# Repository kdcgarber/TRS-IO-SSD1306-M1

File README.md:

# TRS-IO with a SSD1306 LCD display for my Model 1
<br>

These are my notes for the build of this version of my TRS-IO<br>
This repo is, like my other repo, based on a snapshot of https://github.com/apuder/TRS-IO commit f2acde6.<br>
That original repo is an amazing piece of hardware/software that provides new feature to my retro TRS-80 model 1<br>
Thanks for making that project hardware design and code avialable for others like me to use on our retro machines.

I’ve built several TRS-IO boards (the earlier versions are on my other GitHub repo), and I’ve now rebuilt them using this updated design.<br>

One challenge I ran into was keeping track of the IP address for each my TRS-IO's.<br>
So, when multiple TRS-IO units are powered on at the same time, it becomes difficult to know which device you’re actually connected to.<br>

To solve that —and mostly just for fun and to learn more— I extended the original design to include a small status display.<br>
This makes it easy to see the assigned IP address and other useful information directly from the TRS-IO itself.<br>

Because this codebase has diverged from the original TRS-IO backported source, I can no longer pull an upstream updates if there are any.<br>
If the original repository is updated in the future, those changes won’t be reflected here unless manually merged.<br>
That said, most current development in this space appears to be shifting toward TRS-IO++, so upstream changes may be minimal going forward.<br>

These notes document the steps I took to configure this new hardware design with my modified software.<br>
They are just notes. They’re primarily for my own reference, but they may also be helpful to others following a similar path.<br>

The new, smaller PCB files that include the display are available in this repo.<br>

The only real difference for the hardware of my board is the part layout <br>
and removing the LED and its resistors to be replaced with a SSD1306 display. <br>
Any TRS-IO could be changed to replace the LED, it just has no mount to hold the display in place, though one can be created. <br>

<table>
  <tr>
	<td></td>
	<td></td>
  </tr>
</table>

<bre>

## 📂 Content in repository

	.
	├── DebugNotes.txt                       - Notes to setup my PC to view output from the ESP-WROOM-32 usb port
	├── SDcardM1auto.zip                     - SD card files for the SMB share
	├── 3d                                   - STL files to 3D print a case for the new TRS-IO-SSD1306
	├── buildFiles                           - FPGA file
	├── doc                                  - Doc from the original site
	├── examples                             - Code samples form the Orignal Site
	├── images                               - Images for the github pages
	├── kicad-SSD1306                        - Contains the kicad data for the project PCB
	├── src                                  - This is the altered code for the ESP-WROOM-32
	└── src/esp/ESP-WROOOM-32-Deployment     - Compiled Binary ESP files ready for deployment

<br>

## The hardware build and BOM

All of the files for the PCB are in the kicad-SSD1306 directory.<br>
I sent the files to PCBWay to have them created.<br>
Since you pay per square millimeter of board, by placing all the surface mount components on the back sidek, I saved money on the board cost.<br>
In my final builds I opted to mount the FPGA, ESP32, and display directly to the board to decrease the thickness of the board.<br>
I've done both ways, but in the end, since these are dedicated to this, I went with directly soldering them with no sockets.<br>

<table>
  <tr>
    <td></td>
    <td></td>
    <td></td>
  </tr>
  <tr>
    <td></td>
    <td></td>
  </tr>
</table>

<br>
The BOM shows the parts needed and their layout and placement.<br>

<a href="https://kdcgarber.github.io/githubPages-htmlfiles/TRS-IO-SSD1306%20bom/ibom.html" target="_blank">Parts list.</a>
<br>

## There are two paths to get the code deployed to your ESP-WROOM-32.

1 Build the files from source and deploy.<br>
2 Just use the pre-built files to flash your ESP.<br>

<br>
<br>

## Option 1 - The Software build for the ESP-WROOM-32

These notes for the code build are based on the original notes of my TRS-IO build.<br>
The code in this repo already has my code changes in it, so no to alter any code by hand.<br>
I built this for my enjoyment and to learn and have fun.<br>
These changes may not be the best code they could be, but if anyone wants to use it, they can.<br>

I used the ESP-WROOM-32 esp controller (no PSRAM) - https://www.amazon.com/dp/B0B764963C<br>
And I used the Tang Nano 9K FPGA - https://www.aliexpress.us/item/3256804089255675.html<br>

I did this code build on Ubuntu 24.04, as a non-root account<br>

### Prep - installing required components<br>
&nbsp;&nbsp;&nbsp;&nbsp;sudo apt upgrade<br>
### Packages for Espressif<br>
&nbsp;&nbsp;&nbsp;&nbsp;sudo apt-get install git wget flex bison gperf python3 python3-pip python3-setuptools cmake ninja-build ccache libffi-dev libssl-dev dfu-util libusb-1.0-0 python3-virtualenv<br>
###  Packages for TRS-IO<br>
&nbsp;&nbsp;&nbsp;&nbsp;sudo apt-get install z80asm sdcc sdcc-libraries<br>
###  Some fixes for linking libraries that are needed by TRS-IO<br>
&nbsp;&nbsp;&nbsp;&nbsp;sudo mkdir -p /lib/z80/<br>
&nbsp;&nbsp;&nbsp;&nbsp;sudo ln -s /usr/share/sdcc/lib/z80/z80.lib /lib/z80/z80.lib<br>
###  Python3 as default:<br>
&nbsp;&nbsp;&nbsp;&nbsp;sudo apt-get install python3 python3-pip python3-setuptools<br>
&nbsp;&nbsp;&nbsp;&nbsp;sudo ln -s /usr/bin/python3 /usr/bin/python<br>
<br>

###  Install ESP-IDF<br>
cd ~/<br>
mkdir esp<br>
cd esp<br>
git clone -b v4.4.7 --recurse-submodules https://github.com/espressif/esp-idf.git<br>
cd ~/esp/esp-idf<br>
./install.sh esp32<br>

### clone this repo
cd ~/esp<br>
git clone --recurse-submodules https://github.com/kdcgarber/TRS-IO-SSD1306-M1.git<br>

### TRS-IO stuff<br>
.  ~/esp/esp-idf/export.sh<br>

## Compile and Flash the ESP<br>
cd ~/esp/TRS-IO-SSD1306-M1/src/esp<br>
idf.py fullclean<br>
make BOARD=trs-io-m1-v14 build<br>

The build will show many warnings, but if it completes with no errors, the rest should be good.<br>
At the bottom of its output, it lists the command to run. The port needs to be changed to match the correct port.<br>

Sometimes while doing the flash, it fails. If it does, just try it again and it will load.<br><br>
~/esp/esp-idf/components/esptool_py/esptool/esptool.py -p /dev/ttyUSB0  -b 460800 --before default_reset --after hard_reset --chip esp32  write_flash --flash_mode dio --flash_size detect --flash_freq 40m 0x1000 build/bootloader/bootloader.bin 0x8000 build/partition_table/partition-table.bin 0x10000 build/trs-io.bin 0x190000 build/html.bin<br>

<br><br><br>

## 💾 Option 2 - Just use the pre-built bin files
<br>
This path is to flash the ESP-WROOM-32 from the provided files without a full code rebuild. <br>
The code does not need to be recompiled unless you are making changes or just want to.
This directory contains 4 files that are the files needed for the ESP: src/esp/ESP-WROOOM-32-Deployment<br>
<br>
• bootloader.bin<br>
• html.bin<br>
• partition-table.bin<br>
• trs-io.bin<br>
<br>

To use these files you'll need to to install ESPTOOL and then deploy the code.<br>
I did my file flash from the files via a windows 11 PC.<br>

From a windows command shell (CMD)<br>
### Check that Python and PIP are installed and install if they are not found. 
python --version<br>
&nbsp;&nbsp;Python 3.12.10<br>

pip --version <br>
&nbsp;&nbsp;pip 25.3 from C:\Users\toddr\AppData\Local\Packages\PythonSoftwareFoundation.Python.3.12_qbz5n2kfra8p0\LocalCache\local-packages\Python312\site-packages\pip (python 3.12)<br>

### This installs the ESPTOOL
pip install esptool<br>

### Add a shortcut to get to the path to use the ESPTOOL
doskey esptool="C:\Users\toddr\AppData\Local\Packages\PythonSoftwareFoundation.Python.3.12_qbz5n2kfra8p0\LocalCache\local-packages\Python312\Scripts\esptool.exe" $* <br>

ESPTOOL should now work<br>

Just enter "esptool", it should give the default help windows message<br>
Plug your ESP-WROOM-32 in via the usb port to your windows 11 pc.<br>

### Now to find the COM port
With the esp plugged into the laptop in windows 11, "mode" will show the COM it's connected to.<br>
The COM will need to be used on the flash command<br>

mode<br>

Status for device COM5:<br>
Baud:            115200<br>
Parity:          None<br>
Data Bits:       8<br>
Stop Bits:       1<br>
Timeout:         OFF<br>
XON/XOFF:        OFF<br>
CTS handshaking: OFF<br>
DSR handshaking: OFF<br>
DSR sensitivity: OFF<br>
DTR circuit:     OFF<br>
RTS circuit:     OFF<br>
<br>

### Move to your code repo and move to the src/esp/ directory. <br>
cd "C:\Users\toddr\OneDrive\Shared\Todd\GitHub\trsnic-ssd1306\src\esp"<br>

There will be 4 bin files in the directory ESP-WROOOM-32-Deployment which will be flashed to the ESP. <br>
 ### Run this command
(Replace COM5 with your actual COM port number if necessary.) <br>

esptool --chip esp32 --port COM5 --baud 460800 write-flash --flash-mode dio --flash-size detect --flash-freq 40m -z 0x1000 ESP-WROOOM-32-Deployment\bootloader.bin 0x8000 ESP-WROOOM-32-Deployment\partition-table.bin 0x10000 ESP-WROOOM-32-Deployment\trs-io.bin 0x190000 ESP-WROOOM-32-Deployment\html.bin <br>

This should flash the ESP and it will now be ready to use.<br>

# Flash the FPGA

### Install openFPGALoader

apt install \\<br>
  git \\<br>
  gzip \\<br>
  libftdi1-2 \\<br>
  libftdi1-dev \\<br>
  libhidapi-hidraw0 \\<br>
  libhidapi-dev \\<br>
  libudev-dev \\<br>
  zlib1g-dev \\<br>
  cmake \\<br>
  pkg-config \\<br>
  make \\<br>
  g++

git clone https://github.com/trabucayre/openFPGALoader<br>
cd openFPGALoader<br>
mkdir build<br>
cd build<br>
cmake .. <br>
cmake --build .<br>
make install<br>

### The FPGA file is TRS-IO.fs<br>

cd  ~/esp/buildFiles<br>
openFPGALoader -b tangnano9k -f TRS-IO.fs

	EXAMPLE:
	root@thebox:/home/kdcgarber/esp/buildFiles# openFPGALoader -b tangnano9k -f TRS-IO.fs

	empty
	write to flash
	Jtag frequency : requested 6.00MHz   -> real 6.00MHz
	Parse file Parse TRS-IO.fs:
	Done
	DONE
	Jtag frequency : requested 2.50MHz   -> real 2.00MHz
	Erase SRAM DONE
	Erase FLASH DONE
	Erasing FLASH: [==================================================] 100.00%
	Done
	write Flash: [==================================================] 100.00%
	Done
	CRC check: Success

<br>

* There is also a newer version of the TRS-IO.fs that I now use. It provides higher resolution glyphs that can be used instead of the original TRS-IO.fs file. It is called TRS-IO-v1_4-HiRes.fs and can be flashed to replace the TRS-IO.fs I used originally.  
openFPGALoader -b tangnano9k -f TRS-IO-v1_4-HiRes.fs

## All done with the Install

After the install is complete, follow the notes on the TRS-IO site to bring up the trs-io.local access point<br> 
and start the configuration.<br>
The site also has the ROM boot loader for the FreHD to go on the SD card<br>
or the SMB (windows share or for me SAMBA share on my Linux server).<br>

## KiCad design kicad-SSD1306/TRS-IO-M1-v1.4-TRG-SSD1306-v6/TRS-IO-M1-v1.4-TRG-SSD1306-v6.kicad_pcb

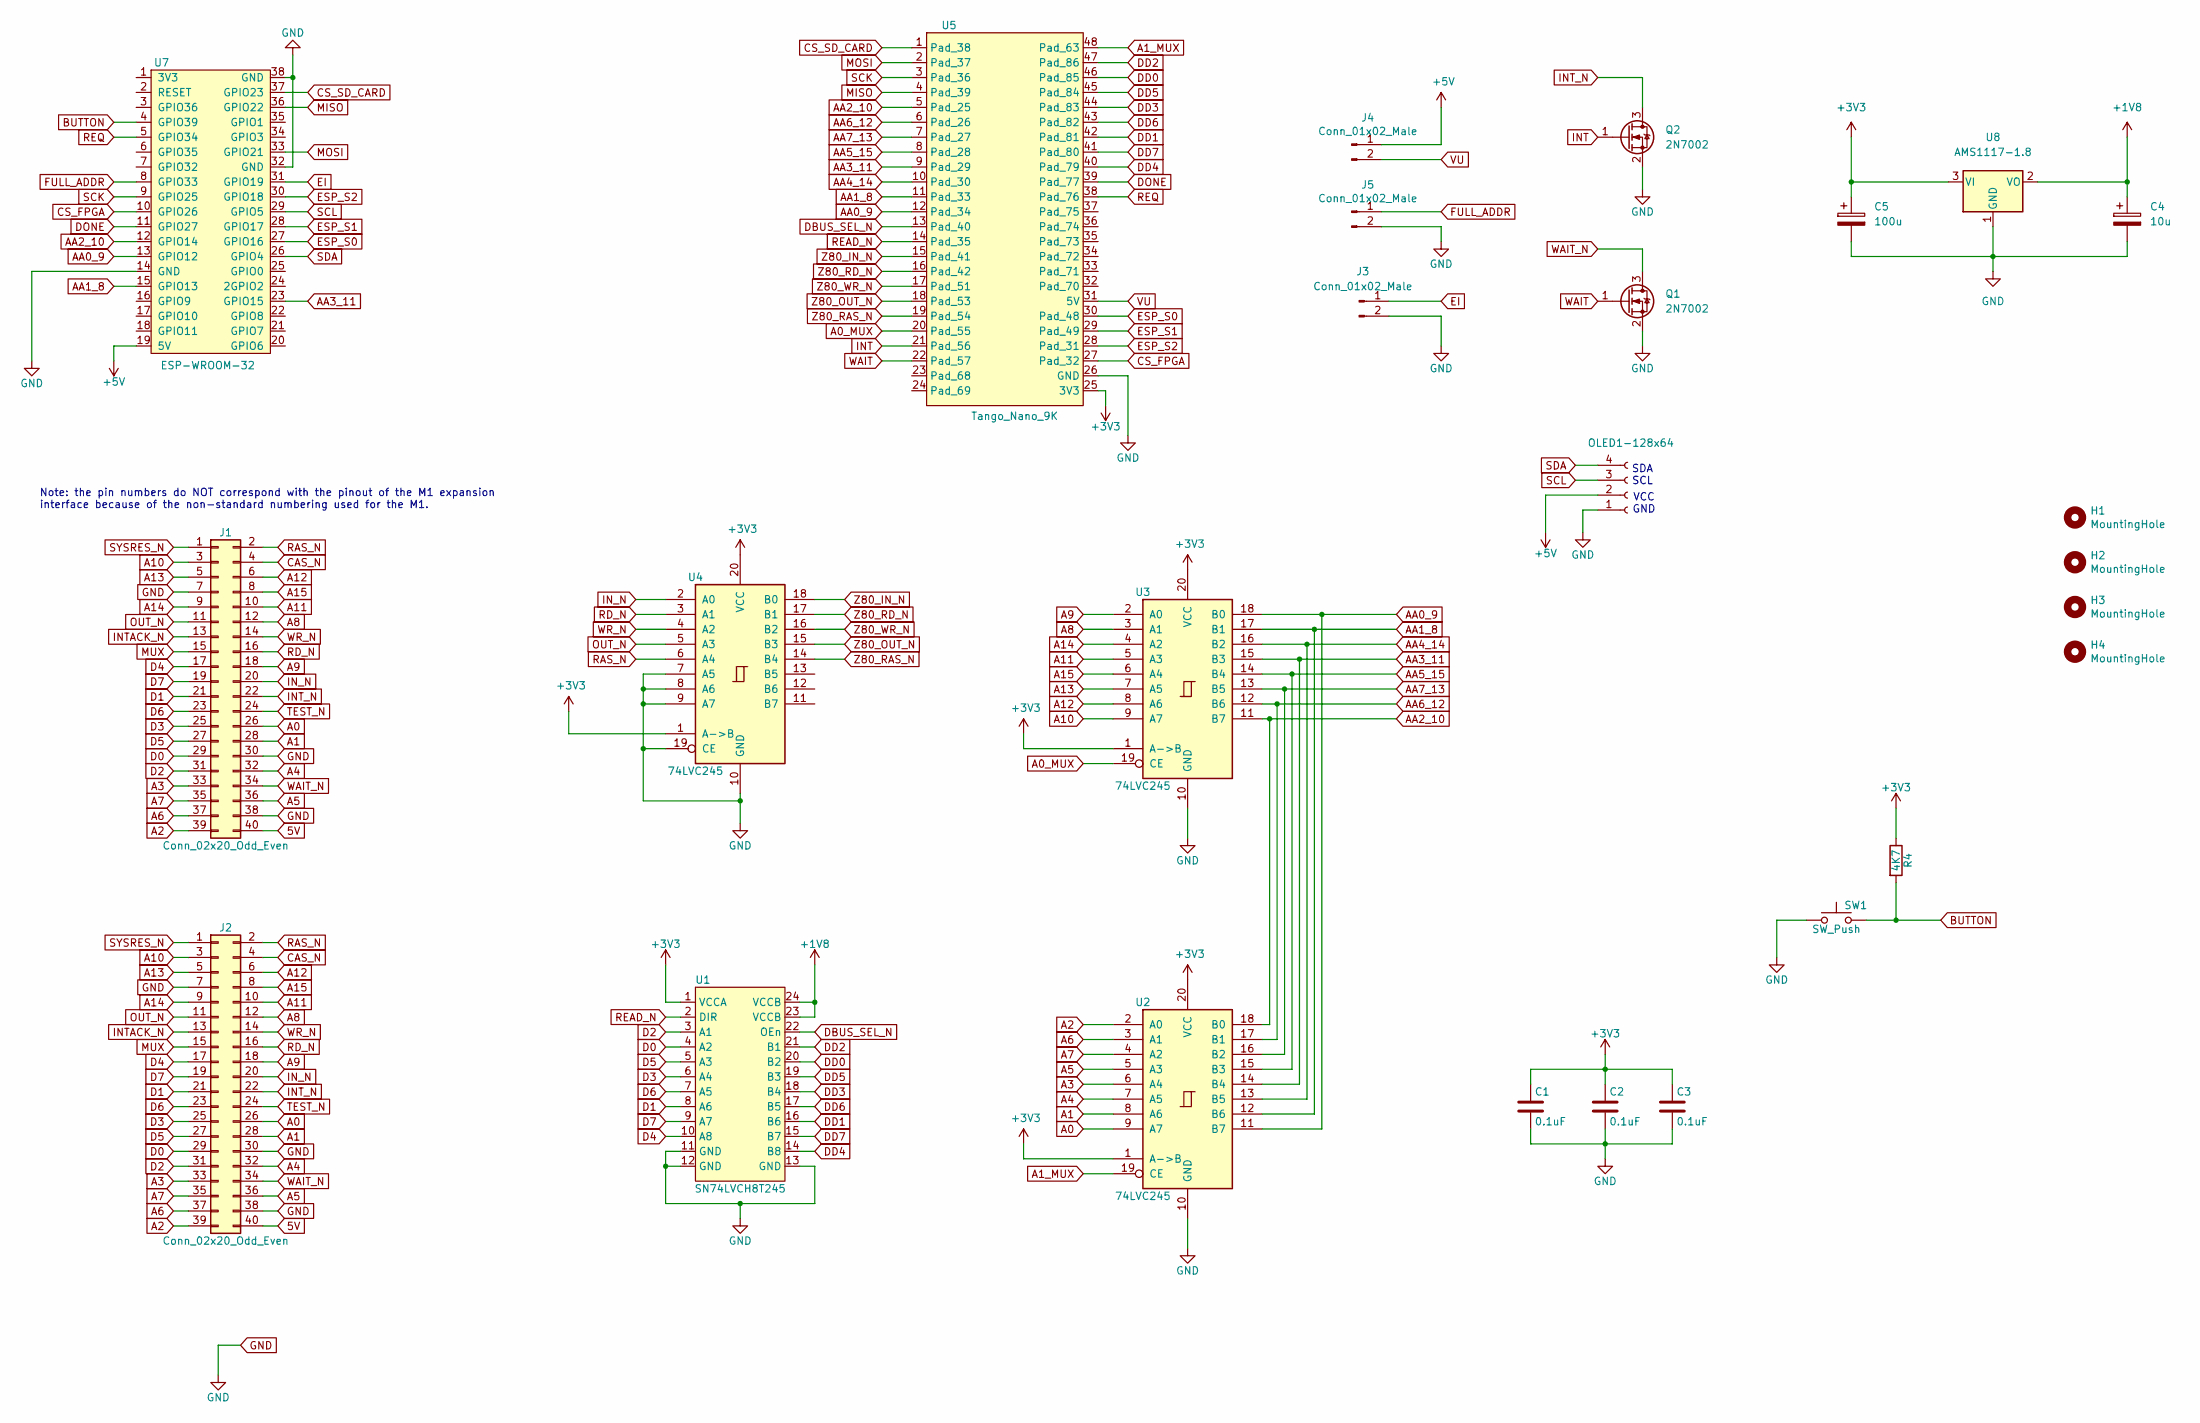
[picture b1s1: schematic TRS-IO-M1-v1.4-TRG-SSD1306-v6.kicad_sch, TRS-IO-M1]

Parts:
C1, C2, C3: 0.1uF; C_0805_2012Metric_Pad1.18x1.45mm_HandSolder
C4: 10u; C_1206_3216Metric_Pad1.33x1.80mm_HandSolder
C5: 100u; C_1206_3216Metric_Pad1.33x1.80mm_HandSolder
H1, H2, H3, H4: MountingHole; MountingHole_3mm_Pad_Via
J1: Conn_02x20_Odd_Even; PinHeader_2x20_P2.54mm_Vertical
J2: Conn_02x20_Odd_Even; TRSEDGE
J3, J4, J5: Conn_01x02_Male; PinHeader_1x02_P2.54mm_Vertical
OLED1-128x64: Conn_01x04_Socket; PinSocket_1x04_P2.54mm_Vertical
Q1, Q2: 2N7002; SOT-23
R4: 4K7; R_0805_2012Metric_Pad1.20x1.40mm_HandSolder
SW1: SW_Push; SW_PUSH_6mm_H9.5mm
U1: SN74LVCH8T245; TSSOP-24_4.4x7.8mm_P0.65mm
U2, U3, U4: 74LVC245; SSOP-20_5.3x7.2mm_P0.65mm_slim
U5: Tango_Nano_9K; DIP-48_W22.9mm
U7: ESP-WROOM-32; DIP-38_W22.9mm
U8: AMS1117-1.8; SOT-223-3_TabPin2

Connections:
5V: J1.40, J2.40
+1V8: C4.1, U1.23 (VCCB), U1.24 (VCCB), U8.2 (VO)
+3V3: C1.1, C2.1, C3.1, C5.1, R4.1, U1.1 (VCCA), U2.1 (A->B), U2.20 (VCC), U3.1 (A->B), U3.20 (VCC), U4.1 (A->B), U4.20 (VCC), U5.25 (3V3), U8.3 (VI)
+5V: J4.1, OLED1-128x64.2, U7.19 (5V); also elsewhere on the board
A0: J1.26, J2.26, U2.9 (A7)
A0_MUX: U3.19 (CE), U5.20 (Pad_55)
A1: J1.28, J2.28, U2.8 (A6)
A1_MUX: U2.19 (CE), U5.48 (Pad_63)
A2: J1.39, J2.39, U2.2 (A0)
A3: J1.33, J2.33, U2.6 (A4)
A4: J1.32, J2.32, U2.7 (A5)
A5: J1.36, J2.36, U2.5 (A3)
A6: J1.37, J2.37, U2.3 (A1)
A7: J1.35, J2.35, U2.4 (A2)
A8: J1.12, J2.12, U3.3 (A1)
A9: J1.18, J2.18, U3.2 (A0)
A10: J1.3, J2.3, U3.9 (A7)
A11: J1.10, J2.10, U3.5 (A3)
A12: J1.6, J2.6, U3.8 (A6)
A13: J1.5, J2.5, U3.7 (A5)
A14: J1.9, J2.9, U3.4 (A2)
A15: J1.8, J2.8, U3.6 (A4)
AA0_9: U2.11 (B7), U3.18 (B0), U5.12 (Pad_34), U7.13 (GPIO12)
AA1_8: U2.12 (B6), U3.17 (B1), U5.11 (Pad_33), U7.15 (GPIO13)
AA2_10: U2.18 (B0), U3.11 (B7), U5.5 (Pad_25), U7.12 (GPIO14)
AA3_11: U2.14 (B4), U3.15 (B3), U5.9 (Pad_29), U7.23 (GPIO15)
AA4_14: U2.13 (B5), U3.16 (B2), U5.10 (Pad_30)
AA5_15: U2.15 (B3), U3.14 (B4), U5.8 (Pad_28)
AA6_12: U2.17 (B1), U3.12 (B6), U5.6 (Pad_26)
AA7_13: U2.16 (B2), U3.13 (B5), U5.7 (Pad_27)
BUTTON: R4.2, SW1.2, U7.4 (GPIO39)
CAS_N: J1.4, J2.4
CS_FPGA: U5.27 (Pad_32), U7.10 (GPIO26)
CS_SD_CARD: U5.1 (Pad_38), U7.37 (GPIO23)
D0: J1.29, J2.29, U1.4 (A2)
D1: J1.21, J2.21, U1.8 (A6)
D2: J1.31, J2.31, U1.3 (A1)
D3: J1.25, J2.25, U1.6 (A4)
D4: J1.17, J2.17, U1.10 (A8)
D5: J1.27, J2.27, U1.5 (A3)
D6: J1.23, J2.23, U1.7 (A5)
D7: J1.19, J2.19, U1.9 (A7)
DBUS_SEL_N: U1.22 (OEn), U5.13 (Pad_40)
DD0: U1.20 (B2), U5.46 (Pad_85)
DD1: U1.16 (B6), U5.42 (Pad_81)
DD2: U1.21 (B1), U5.47 (Pad_86)
DD3: U1.18 (B4), U5.44 (Pad_83)
DD4: U1.14 (B8), U5.40 (Pad_79)
DD5: U1.19 (B3), U5.45 (Pad_84)
DD6: U1.17 (B5), U5.43 (Pad_82)
DD7: U1.15 (B7), U5.41 (Pad_80)
DONE: U5.39 (Pad_77), U7.11 (GPIO27)
EI: J3.1, U7.31 (GPIO19)
ESP_S0: U5.30 (Pad_48), U7.27 (GPIO16)
ESP_S1: U5.29 (Pad_49), U7.28 (GPIO17)
ESP_S2: U5.28 (Pad_31), U7.30 (GPIO18)
FULL_ADDR: J5.1, U7.8 (GPIO33)
GND: C1.2, C2.2, C3.2, C4.2, C5.2, J1.7, J1.30, J1.38, J2.7, J2.30, J2.38, J3.2, J5.2, OLED1-128x64.1, Q1.2 (S), Q2.2 (S), SW1.1, U1.11 (GND), U1.12 (GND), U1.13 (GND), U2.10 (GND), U3.10 (GND), U4.7 (A5), U4.8 (A6), U4.9 (A7), U4.10 (GND), U4.19 (CE), U5.26 (GND), U7.14 (GND), U7.32 (GND), U7.38 (GND), U8.1 (GND); also elsewhere on the board
INT: Q2.1 (G), U5.21 (Pad_56)
INTACK_N: J1.13, J2.13
INT_N: J1.22, J2.22, Q2.3 (D)
IN_N: J1.20, J2.20, U4.2 (A0)
MISO: U5.4 (Pad_39), U7.36 (GPIO22)
MOSI: U5.2 (Pad_37), U7.33 (GPIO21)
MUX: J1.15, J2.15
OUT_N: J1.11, J2.11, U4.5 (A3)
RAS_N: J1.2, J2.2, U4.6 (A4)
RD_N: J1.16, J2.16, U4.3 (A1)
READ_N: U1.2 (DIR), U5.14 (Pad_35)
REQ: U5.38 (Pad_76), U7.5 (GPIO34)
SCK: U5.3 (Pad_36), U7.9 (GPIO25)
SCL: OLED1-128x64.3, U7.29 (GPIO5); also elsewhere on the board
SDA: OLED1-128x64.4, U7.26 (GPIO4); also elsewhere on the board
SYSRES_N: J1.1, J2.1
TEST_N: J1.24, J2.24
VU: J4.2, U5.31 (5V)
WAIT: Q1.1 (G), U5.22 (Pad_57)
WAIT_N: J1.34, J2.34, Q1.3 (D)
WR_N: J1.14, J2.14, U4.4 (A2)
Z80_IN_N: U4.18 (B0), U5.15 (Pad_41)
Z80_OUT_N: U4.15 (B3), U5.18 (Pad_53)
Z80_RAS_N: U4.14 (B4), U5.19 (Pad_54)
Z80_RD_N: U4.17 (B1), U5.16 (Pad_42)
Z80_WR_N: U4.16 (B2), U5.17 (Pad_51)

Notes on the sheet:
VCC GND
SDA SCL
Note: the pin numbers do NOT correspond with the pinout of the M1 expansion interface because of the non-standard numbering used for the M1.

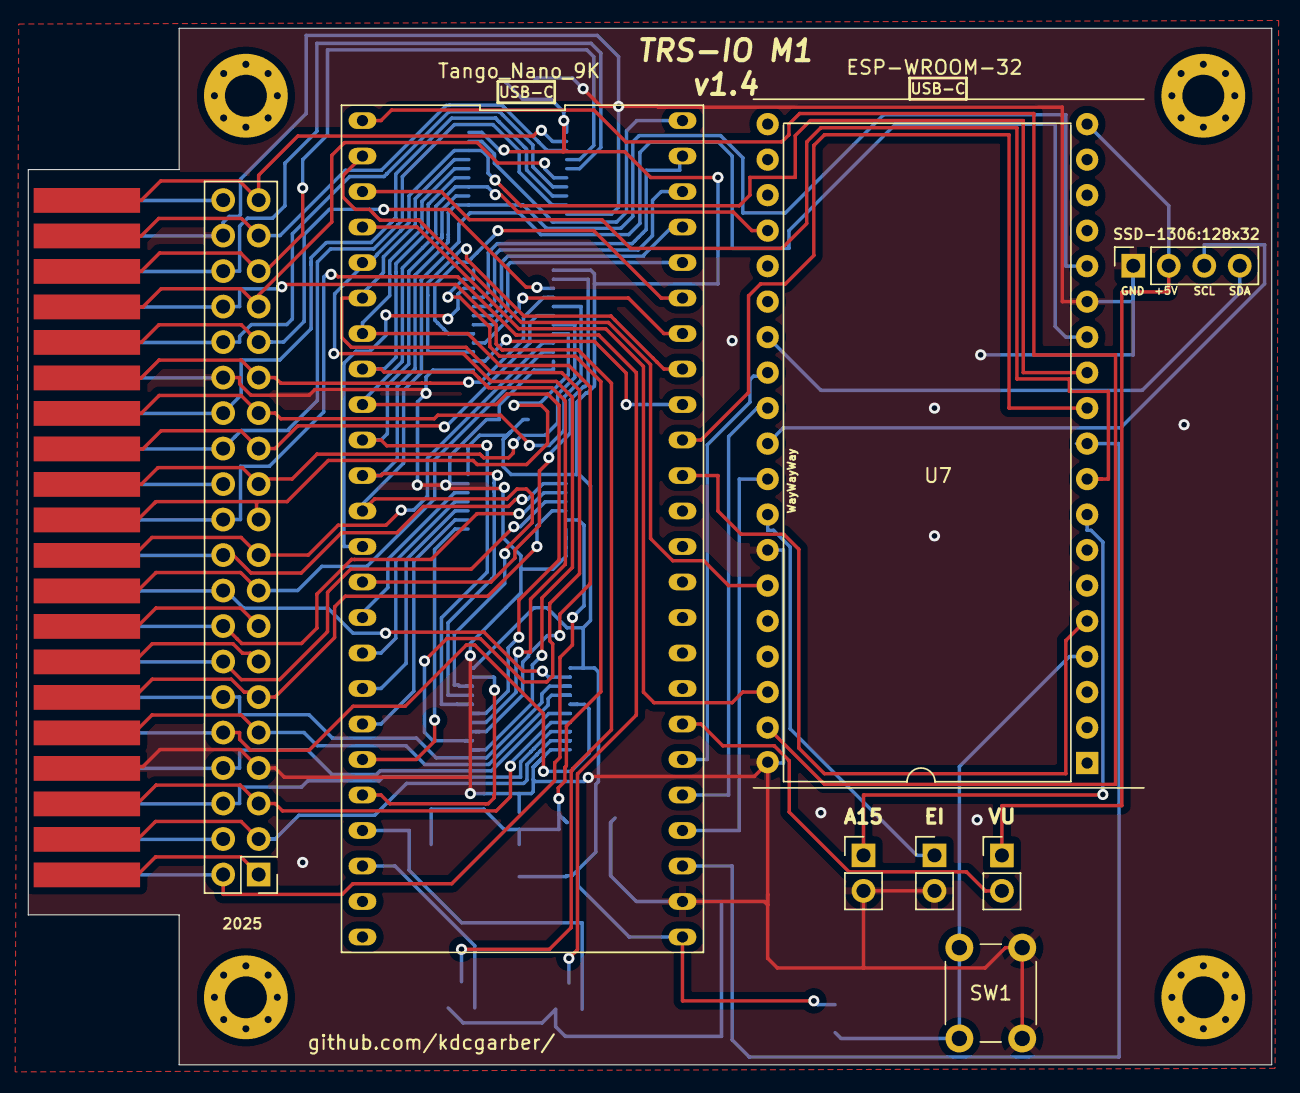
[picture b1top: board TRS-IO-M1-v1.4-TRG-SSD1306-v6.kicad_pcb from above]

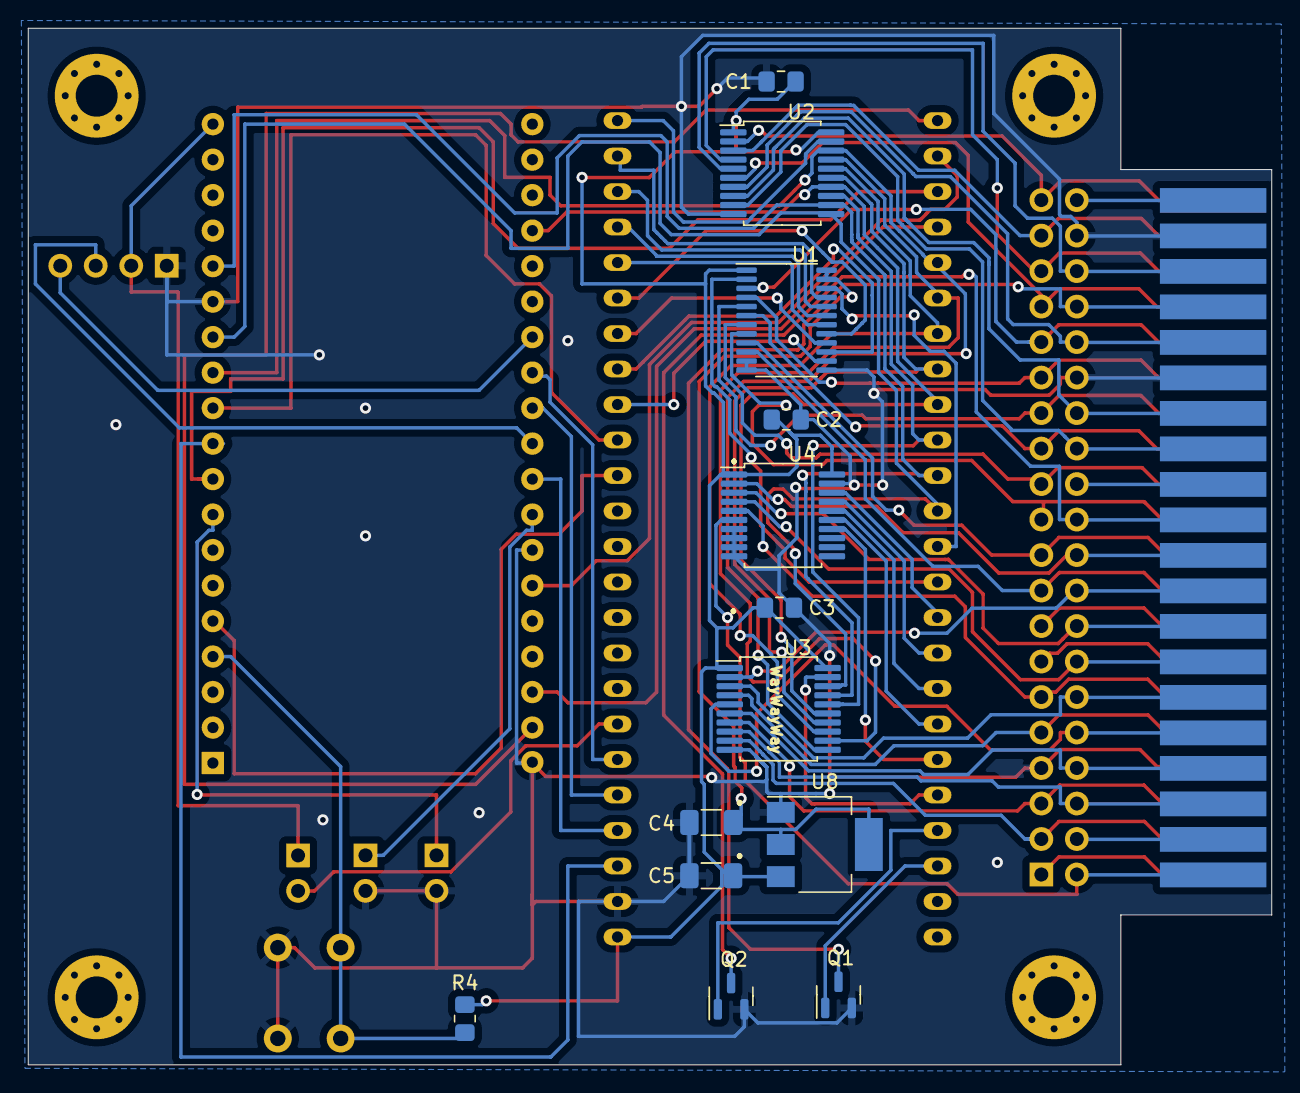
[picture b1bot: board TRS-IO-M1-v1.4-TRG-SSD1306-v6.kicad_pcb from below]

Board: 2 copper layers, 89.0 x 74.2 mm, 26 parts (13 on the bottom side), 84 nets.

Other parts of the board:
SSD-1306:128x32: Conn_01x04_Socket; PinSocket_1x04_P2.54mm_Vertical

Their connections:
+5V: SSD-1306:128x32.2; also elsewhere on the board
GND: SSD-1306:128x32.1; also elsewhere on the board
SCL: SSD-1306:128x32.3; also elsewhere on the board
SDA: SSD-1306:128x32.4; also elsewhere on the board

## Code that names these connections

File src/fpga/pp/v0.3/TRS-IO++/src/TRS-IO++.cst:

//Copyright (C)2014-2022 Gowin Semiconductor Corporation.
//All rights reserved. 
//File Title: Physical Constraints file
//GOWIN Version: 1.9.8.09
//Part Number: GW2A-LV18PG256C8/I7
//Device: GW2A-18C
//Created Time: Wed 01 25 21:33:22 2023

IO_LOC "CTRL1_EN" D10;
IO_PORT "CTRL1_EN" IO_TYPE=LVCMOS33 PULL_MODE=UP DRIVE=8;
IO_LOC "EXTIOSEL" D11;
IO_PORT "EXTIOSEL" IO_TYPE=LVCMOS33 PULL_MODE=DOWN DRIVE=8;
IO_LOC "WAIT" F10;
IO_PORT "WAIT" IO_TYPE=LVCMOS33 PULL_MODE=DOWN DRIVE=8;
IO_LOC "INT" J11;
IO_PORT "INT" IO_TYPE=LVCMOS33 PULL_MODE=DOWN DRIVE=8;
IO_LOC "INT_IN_N" P7;
IO_PORT "INT_IN_N" IO_TYPE=LVCMOS33 PULL_MODE=UP;
IO_LOC "LED_BLUE" A9;
IO_PORT "LED_BLUE" IO_TYPE=LVCMOS33 PULL_MODE=UP DRIVE=8;
IO_LOC "LED_RED" L12;
IO_PORT "LED_RED" IO_TYPE=LVCMOS33 PULL_MODE=UP DRIVE=8;
IO_LOC "LED_GREEN" C9;
IO_PORT "LED_GREEN" IO_TYPE=LVCMOS33 PULL_MODE=UP DRIVE=8;
IO_LOC "VIDEO_O" L9;
IO_PORT "VIDEO_O" IO_TYPE=LVCMOS33 PULL_MODE=UP DRIVE=8;
IO_LOC "VSYNC_O" N8;
IO_PORT "VSYNC_O" IO_TYPE=LVCMOS33 PULL_MODE=UP DRIVE=8;
IO_LOC "HSYNC_O" R9;
IO_PORT "HSYNC_O" IO_TYPE=LVCMOS33 PULL_MODE=UP DRIVE=8;
IO_LOC "LED[3]" F15;
IO_PORT "LED[3]" IO_TYPE=LVCMOS33 PULL_MODE=UP DRIVE=8;
IO_LOC "LED[2]" C13;
IO_PORT "LED[2]" IO_TYPE=LVCMOS33 PULL_MODE=UP DRIVE=8;
IO_LOC "LED[1]" D16;
IO_PORT "LED[1]" IO_TYPE=LVCMOS33 PULL_MODE=UP DRIVE=8;
IO_LOC "LED[0]" E14;
IO_PORT "LED[0]" IO_TYPE=LVCMOS33 PULL_MODE=UP DRIVE=8;
IO_LOC "REQ" A13;
IO_PORT "REQ" IO_TYPE=LVCMOS33 PULL_MODE=UP DRIVE=8;
IO_LOC "ESP_S[3]" B10;
IO_PORT "ESP_S[3]" IO_TYPE=LVCMOS33 PULL_MODE=UP DRIVE=8;
IO_LOC "ESP_S[2]" G11;
IO_PORT "ESP_S[2]" IO_TYPE=LVCMOS33 PULL_MODE=UP DRIVE=8;
IO_LOC "ESP_S[1]" H12;
IO_PORT "ESP_S[1]" IO_TYPE=LVCMOS33 PULL_MODE=UP DRIVE=8;
IO_LOC "ESP_S[0]" J12;
IO_PORT "ESP_S[0]" IO_TYPE=LVCMOS33 PULL_MODE=UP DRIVE=8;
IO_LOC "CASS_OUT" C10;
IO_PORT "CASS_OUT" IO_TYPE=LVCMOS33 PULL_MODE=UP DRIVE=8;
IO_LOC "DBUS_EN" J16;
IO_PORT "DBUS_EN" IO_TYPE=LVCMOS33 PULL_MODE=UP DRIVE=8;
IO_LOC "DBUS_DIR" T15;
IO_PORT "DBUS_DIR" IO_TYPE=LVCMOS33 PULL_MODE=UP DRIVE=8;
IO_LOC "ABUS_DIR_N" R16;
IO_PORT "ABUS_DIR_N" IO_TYPE=LVCMOS33 PULL_MODE=UP DRIVE=8;
IO_LOC "ABUS_EN" T12;
IO_PORT "ABUS_EN" IO_TYPE=LVCMOS33 PULL_MODE=UP DRIVE=8;
IO_LOC "ABUS_DIR" R11;
IO_PORT "ABUS_DIR" IO_TYPE=LVCMOS33 PULL_MODE=UP DRIVE=8;
IO_LOC "CTRL_EN" P6;
IO_PORT "CTRL_EN" IO_TYPE=LVCMOS33 PULL_MODE=UP DRIVE=8;
IO_LOC "CTRL_DIR" T6;
IO_PORT "CTRL_DIR" IO_TYPE=LVCMOS33 PULL_MODE=UP DRIVE=8;
IO_LOC "MISO" K13;
IO_PORT "MISO" IO_TYPE=LVCMOS33 PULL_MODE=UP DRIVE=8;
IO_LOC "_D[7]" J14;
IO_PORT "_D[7]" IO_TYPE=LVCMOS33 PULL_MODE=UP;
IO_LOC "_D[6]" G14;
IO_PORT "_D[6]" IO_TYPE=LVCMOS33 PULL_MODE=UP;
IO_LOC "_D[5]" G15;
IO_PORT "_D[5]" IO_TYPE=LVCMOS33 PULL_MODE=UP;
IO_LOC "_D[4]" F14;
IO_PORT "_D[4]" IO_TYPE=LVCMOS33 PULL_MODE=UP;
IO_LOC "_D[3]" F16;
IO_PORT "_D[3]" IO_TYPE=LVCMOS33 PULL_MODE=UP;
IO_LOC "_D[2]" E15;
IO_PORT "_D[2]" IO_TYPE=LVCMOS33 PULL_MODE=UP;
IO_LOC "_D[1]" D14;
IO_PORT "_D[1]" IO_TYPE=LVCMOS33 PULL_MODE=UP;
IO_LOC "_D[0]" A15;
IO_PORT "_D[0]" IO_TYPE=LVCMOS33 PULL_MODE=UP;
IO_LOC "_A[15]" N16;
IO_PORT "_A[15]" IO_TYPE=LVCMOS33 PULL_MODE=UP;
IO_LOC "_A[14]" N15;
IO_PORT "_A[14]" IO_TYPE=LVCMOS33 PULL_MODE=UP;
IO_LOC "_A[13]" N14;
IO_PORT "_A[13]" IO_TYPE=LVCMOS33 PULL_MODE=UP;
IO_LOC "_A[12]" L16;
IO_PORT "_A[12]" IO_TYPE=LVCMOS33 PULL_MODE=UP;
IO_LOC "_A[11]" P16;
IO_PORT "_A[11]" IO_TYPE=LVCMOS33 PULL_MODE=UP;
IO_LOC "_A[10]" L14;
IO_PORT "_A[10]" IO_TYPE=LVCMOS33 PULL_MODE=UP;
IO_LOC "_A[9]" L13;
IO_PORT "_A[9]" IO_TYPE=LVCMOS33 PULL_MODE=UP;
IO_LOC "_A[8]" P15;
IO_PORT "_A[8]" IO_TYPE=LVCMOS33 PULL_MODE=UP;
IO_LOC "_A[7]" R12;
IO_PORT "_A[7]" IO_TYPE=LVCMOS33 PULL_MODE=UP;
IO_LOC "_A[6]" P13;
IO_PORT "_A[6]" IO_TYPE=LVCMOS33 PULL_MODE=UP;
IO_LOC "_A[5]" R13;
IO_PORT "_A[5]" IO_TYPE=LVCMOS33 PULL_MODE=UP;
IO_LOC "_A[4]" T14;
IO_PORT "_A[4]" IO_TYPE=LVCMOS33 PULL_MODE=UP;
IO_LOC "_A[3]" M15;
IO_PORT "_A[3]" IO_TYPE=LVCMOS33 PULL_MODE=UP;
IO_LOC "_A[2]" M14;
IO_PORT "_A[2]" IO_TYPE=LVCMOS33 PULL_MODE=UP;
IO_LOC "_A[1]" F13;
IO_PORT "_A[1]" IO_TYPE=LVCMOS33 PULL_MODE=UP;
IO_LOC "_A[0]" G12;
IO_PORT "_A[0]" IO_TYPE=LVCMOS33 PULL_MODE=UP;
IO_LOC "_OUT_N" P8;
IO_PORT "_OUT_N" IO_TYPE=LVCMOS33 PULL_MODE=UP;
IO_LOC "_WR_N" T8;
IO_PORT "_WR_N" IO_TYPE=LVCMOS33 PULL_MODE=UP;
IO_LOC "_RD_N" R8;
IO_PORT "_RD_N" IO_TYPE=LVCMOS33 PULL_MODE=UP;
IO_LOC "_IN_N" T7;
IO_PORT "_IN_N" IO_TYPE=LVCMOS33 PULL_MODE=UP;
IO_LOC "DONE" E16;
IO_PORT "DONE" IO_TYPE=LVCMOS33 PULL_MODE=UP;
IO_LOC "MOSI" H13;
IO_PORT "MOSI" IO_TYPE=LVCMOS33 PULL_MODE=UP;
IO_LOC "SCK" K12;
IO_PORT "SCK" IO_TYPE=LVCMOS33 PULL_MODE=UP;
IO_LOC "CS_FPGA" K11;
IO_PORT "CS_FPGA" IO_TYPE=LVCMOS33 PULL_MODE=UP;
IO_LOC "clk_in" H11;
IO_PORT "clk_in" PULL_MODE=UP;
IO_LOC "HDMI_TXC_P" G16,H15;
IO_PORT "HDMI_TXC_P" PULL_MODE=NONE DRIVE=3.5;
IO_LOC "HDMI_TX_P[0]" H16,H14;
IO_PORT "HDMI_TX_P[0]" PULL_MODE=NONE DRIVE=3.5;
IO_LOC "HDMI_TX_P[1]" K16,J15;
IO_PORT "HDMI_TX_P[1]" PULL_MODE=NONE DRIVE=3.5;
IO_LOC "HDMI_TX_P[2]" K15,K14;
IO_PORT "HDMI_TX_P[2]" PULL_MODE=NONE DRIVE=3.5;
IO_LOC "_M1_N" P11;
IO_PORT "_M1_N" IO_TYPE=LVCMOS33 PULL_MODE=UP DRIVE=8;
IO_LOC "WAIT_IN_N" R7;
IO_PORT "WAIT_IN_N" IO_TYPE=LVCMOS33 PULL_MODE=UP;
IO_LOC "EXTIOSEL_IN_N" E10;
IO_PORT "EXTIOSEL_IN_N" IO_TYPE=LVCMOS33 PULL_MODE=UP;
IO_LOC "VIDEOX" N7;
IO_PORT "VIDEOX" IO_TYPE=LVCMOS33 PULL_MODE=UP;
IO_LOC "CONF[1]" C11;
IO_PORT "CONF[1]" IO_TYPE=LVCMOS33 PULL_MODE=UP;
IO_LOC "HSYNCX" L8;
IO_PORT "HSYNCX" IO_TYPE=LVCMOS33 PULL_MODE=UP;
IO_LOC "_RESET_N" T11;
IO_PORT "_RESET_N" IO_TYPE=LVCMOS33 PULL_MODE=UP DRIVE=8;
IO_LOC "CONF[2]" B11;
IO_PORT "CONF[2]" IO_TYPE=LVCMOS33 PULL_MODE=UP;
IO_LOC "_IOREQ_N" P9;
IO_PORT "_IOREQ_N" IO_TYPE=LVCMOS33 PULL_MODE=UP DRIVE=8;
IO_LOC "CONF[0]" A12;
IO_PORT "CONF[0]" IO_TYPE=LVCMOS33 PULL_MODE=UP DRIVE=16;
IO_LOC "_RAS_N" T9;
IO_PORT "_RAS_N" IO_TYPE=LVCMOS33 PULL_MODE=UP DRIVE=8;
IO_LOC "CONF[3]" A11;
IO_PORT "CONF[3]" IO_TYPE=LVCMOS33 PULL_MODE=UP;
IO_LOC "VSYNCX" M6;
IO_PORT "VSYNCX" IO_TYPE=LVCMOS33 PULL_MODE=UP;

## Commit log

2026-05-12 Fix command syntax for doskey and esptool usage
2026-05-13 Newer TRS-IO-v1_4-HiRes.fs file for higher resolution glyphs.
